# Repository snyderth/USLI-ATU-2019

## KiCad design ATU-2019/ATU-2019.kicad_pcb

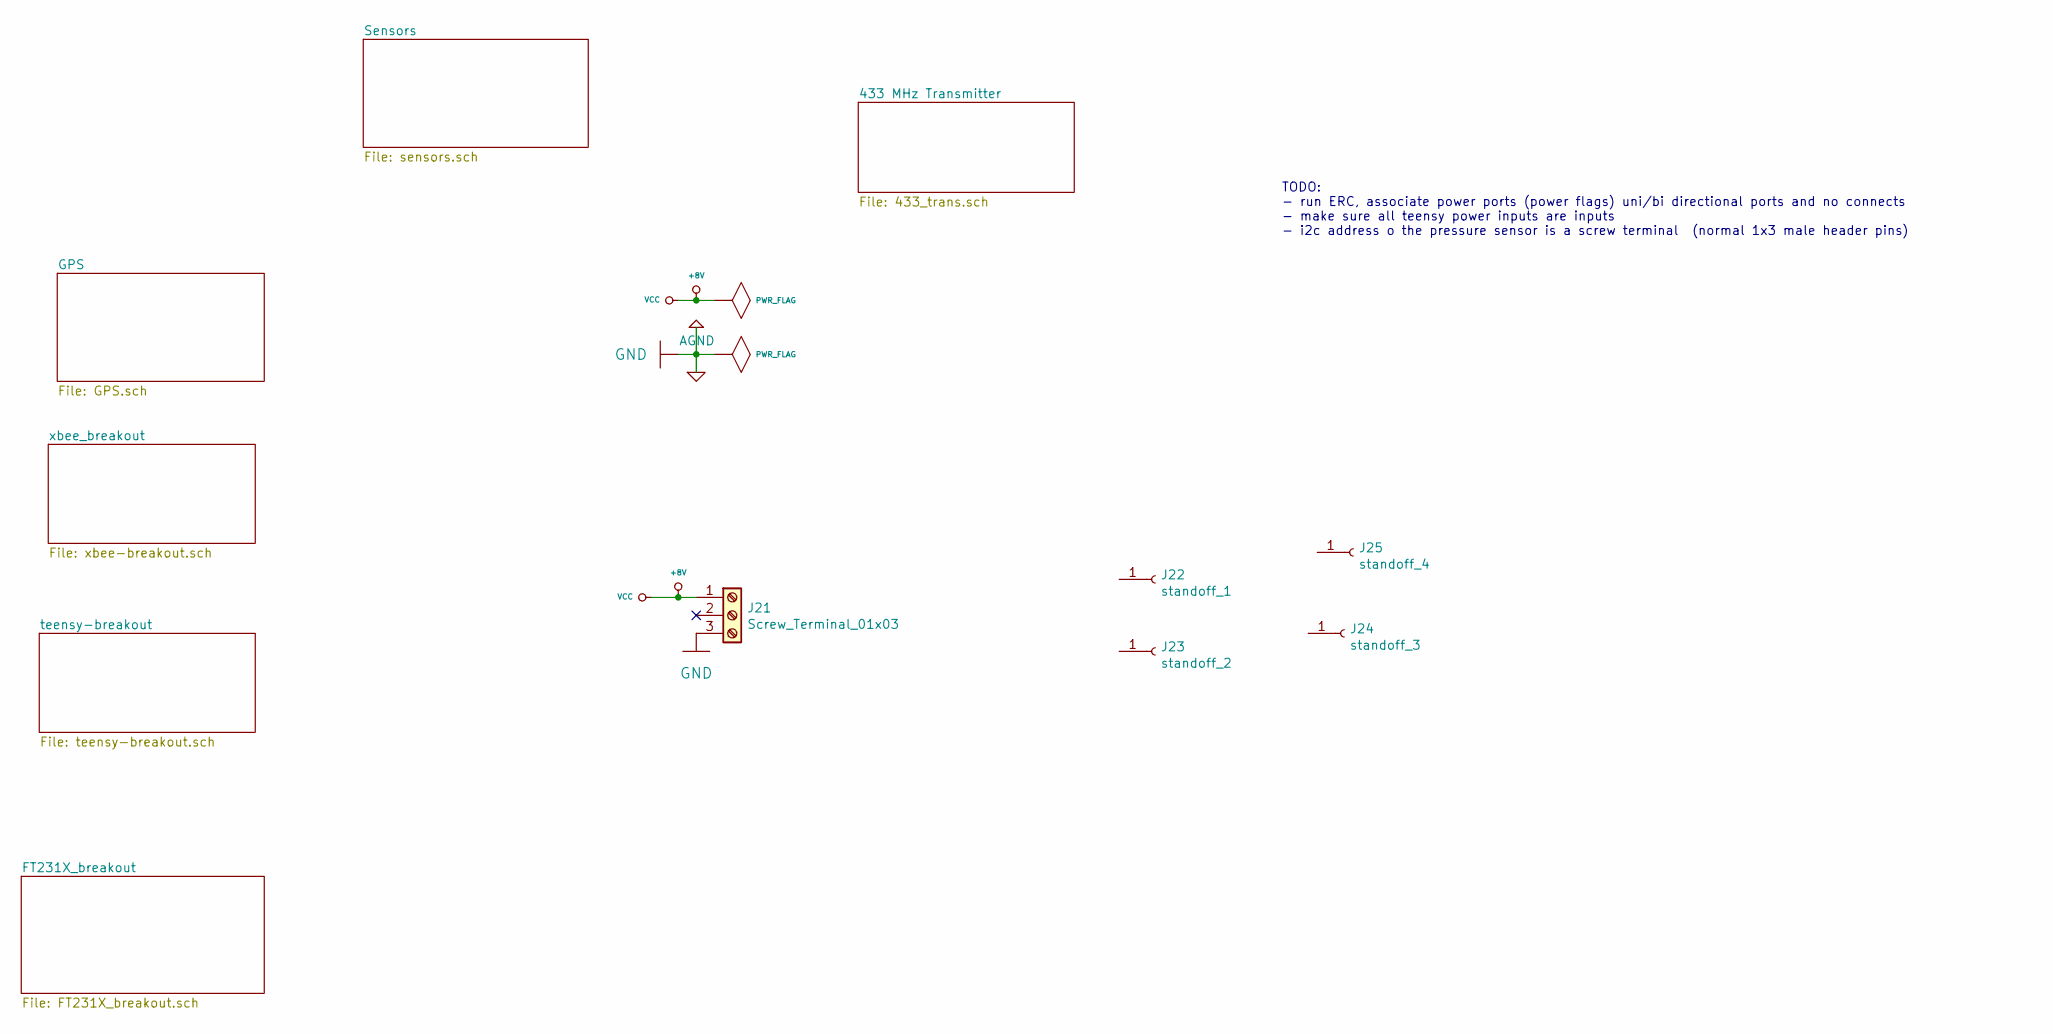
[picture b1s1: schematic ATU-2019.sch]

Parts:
J21: Screw_Terminal_01x03; TerminalBlock_4Ucon_1x03_P3.50mm_Vertical
J22: standoff_1; MountingHole_4.3mm_M4_Pad
J23: standoff_2; MountingHole_4.3mm_M4_Pad
J24: standoff_3; MountingHole_4.3mm_M4_Pad
J25: standoff_4; MountingHole_4.3mm_M4_Pad

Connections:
+8V: J21.1; also elsewhere on the board
AGND: J21.3; also elsewhere on the board

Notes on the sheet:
TODO: - run ERC, associate power ports (power flags) uni/bi directional ports and no connects - make sure all teensy power inputs are inputs - i2c address o the pressure sensor is a screw terminal (normal 1x3 male header pins)

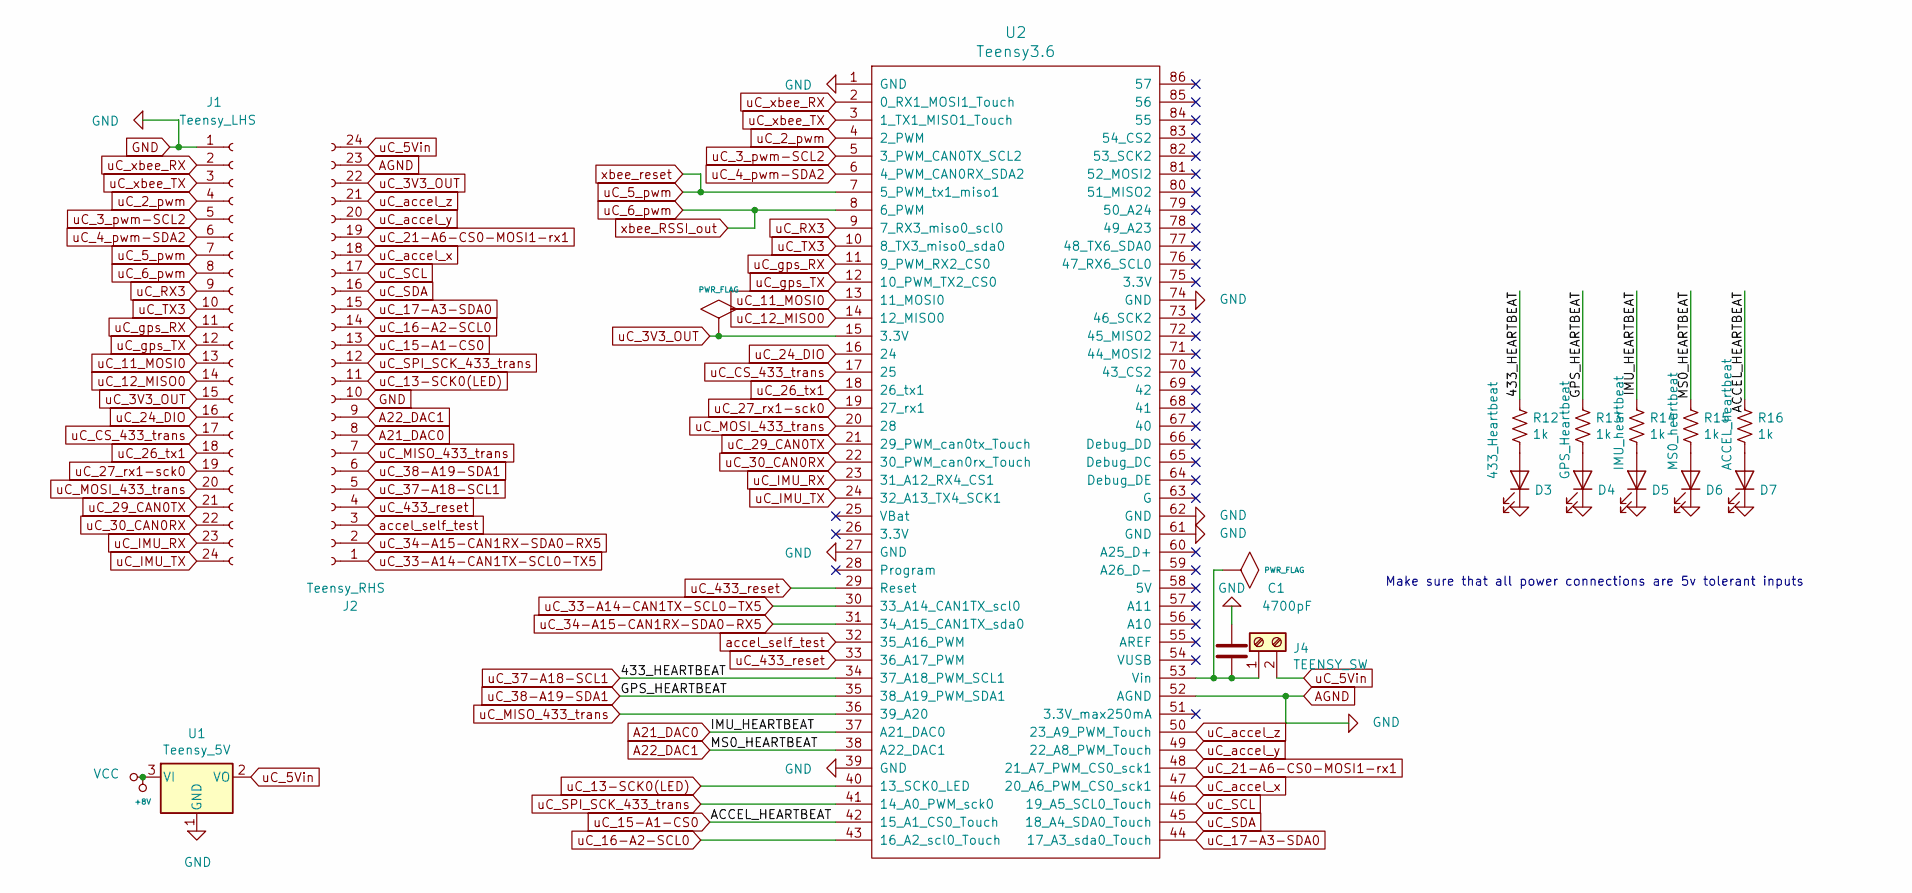
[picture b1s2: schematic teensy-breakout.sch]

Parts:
C1: 4700pF; C_0805_2012Metric_Pad1.15x1.40mm_HandSolder
D3: 433_Heartbeat; LED_0805_2012Metric_Pad1.15x1.40mm_HandSolder
D4: GPS_Heartbeat; LED_0805_2012Metric_Pad1.15x1.40mm_HandSolder
D5: IMU_heartbeat; LED_0805_2012Metric_Pad1.15x1.40mm_HandSolder
D6: MS0_heartbeat; LED_0805_2012Metric_Pad1.15x1.40mm_HandSolder
D7: ACCEL_heartbeat; LED_0805_2012Metric_Pad1.15x1.40mm_HandSolder
J1: Teensy_LHS; PinHeader_1x24_P2.54mm_Vertical
J2: Teensy_RHS; PinHeader_1x24_P2.54mm_Vertical
J4: TEENSY_SW; TerminalBlock_4Ucon_1x02_P3.50mm_Vertical
R12, R13, R14, R15, R16: 1k; R_0805_2012Metric_Pad1.15x1.40mm_HandSolder
U1: Teensy_5V; TO-263-3_TabPin2
U2: Teensy3.6; Teensy35_36

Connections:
+8V: U1.3 (VI); also elsewhere on the board
A21_DAC0: J2.8, R14.1, U2.37 (A21_DAC0)
A22_DAC1: J2.9, R15.1, U2.38 (A22_DAC1)
AGND: C1.2, D3.1 (K), D4.1 (K), D5.1 (K), D6.1 (K), D7.1 (K), J1.1, J2.10, J2.23, U1.1 (GND), U2.1 (GND), U2.27 (GND), U2.39 (GND), U2.52 (AGND), U2.61 (GND), U2.62 (GND), U2.74 (GND); also elsewhere on the board
unnamed: D3.2 (A), R12.2
unnamed: D4.2 (A), R13.2
unnamed: D5.2 (A), R14.2
unnamed: D6.2 (A), R15.2
unnamed: D7.2 (A), R16.2
accel_self_test: J2.3, U2.32 (35_A16_PWM); also elsewhere on the board
uC_2_pwm: J1.4, U2.4 (2_PWM)
uC_3_pwm-SCL2: J1.5, U2.5 (3_PWM_CAN0TX_SCL2)
uC_4_pwm-SDA2: J1.6, U2.6 (4_PWM_CAN0RX_SDA2)
uC_5_pwm: J1.7, U2.7 (5_PWM_tx1_miso1); also elsewhere on the board
uC_6_pwm: J1.8, U2.8 (6_PWM); also elsewhere on the board
uC_11_MOSI0: J1.13, U2.13 (11_MOSI0)
uC_12_MISO0: J1.14, U2.14 (12_MISO0)
uC_13-SCK0(LED): J2.11, U2.40 (13_SCK0_LED)
uC_15-A1-CS0: J2.13, R16.1, U2.42 (15_A1_CS0_Touch)
uC_16-A2-SCL0: J2.14, U2.43 (16_A2_scl0_Touch)
uC_17-A3-SDA0: J2.15, U2.44 (17_A3_sda0_Touch)
uC_21-A6-CS0-MOSI1-rx1: J2.19, U2.48 (21_A7_PWM_CS0_sck1)
uC_24_DIO: J1.16, U2.16 (24)
uC_26_tx1: J1.18, U2.18 (26_tx1)
uC_27_rx1-sck0: J1.19, U2.19 (27_rx1)
uC_29_CAN0TX: J1.21, U2.21 (29_PWM_can0tx_Touch)
uC_30_CAN0RX: J1.22, U2.22 (30_PWM_can0rx_Touch)
uC_33-A14-CAN1TX-SCL0-TX5: J2.1, U2.30 (33_A14_CAN1TX_scl0)
uC_34-A15-CAN1RX-SDA0-RX5: J2.2, U2.31 (34_A15_CAN1TX_sda0)
uC_37-A18-SCL1: J2.5, R12.1, U2.34 (37_A18_PWM_SCL1)
uC_38-A19-SDA1: J2.6, R13.1, U2.35 (38_A19_PWM_SDA1)
uC_CS_433_trans: J1.17, U2.17 (25); also elsewhere on the board
uC_IMU_RX: J1.23, U2.23 (31_A12_RX4_CS1)
uC_IMU_TX: J1.24, U2.24 (32_A13_TX4_SCK1)
uC_MISO_433_trans: J2.7, U2.36 (39_A20); also elsewhere on the board
uC_MOSI_433_trans: J1.20, U2.20 (28); also elsewhere on the board
uC_RX3: J1.9, U2.9 (7_RX3_miso0_scl0)
uC_SCL: J2.17, U2.46 (19_A5_SCL0_Touch); also elsewhere on the board
uC_SDA: J2.16, U2.45 (18_A4_SDA0_Touch); also elsewhere on the board
uC_SPI_SCK_433_trans: J2.12, U2.41 (14_A0_PWM_sck0); also elsewhere on the board
uC_TX3: J1.10, U2.10 (8_TX3_miso0_sda0)
uC_accel_x: J2.18, U2.47 (20_A6_PWM_CS0_sck1); also elsewhere on the board
uC_accel_y: J2.20, U2.49 (22_A8_PWM_Touch); also elsewhere on the board
uC_accel_z: J2.21, U2.50 (23_A9_PWM_Touch); also elsewhere on the board
uC_gps_RX: J1.11, U2.11 (9_PWM_RX2_CS0); also elsewhere on the board
uC_gps_TX: J1.12, U2.12 (10_PWM_TX2_CS0); also elsewhere on the board
uC_xbee_RX: J1.2, U2.2 (0_RX1_MOSI1_Touch); also elsewhere on the board
uC_xbee_TX: J1.3, U2.3 (1_TX1_MISO1_Touch); also elsewhere on the board

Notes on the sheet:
Make sure that all power connections are 5v tolerant inputs

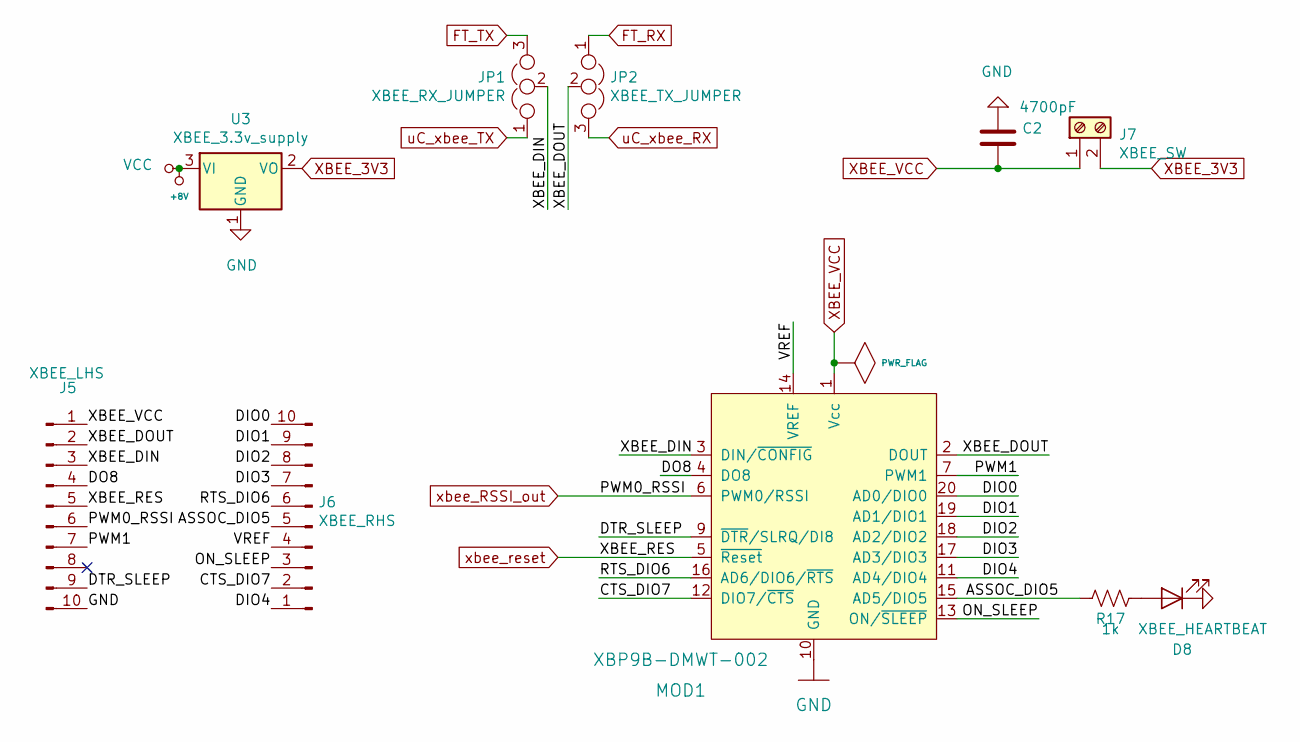
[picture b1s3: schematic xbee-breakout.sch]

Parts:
C2: 4700pF; C_0805_2012Metric_Pad1.15x1.40mm_HandSolder
D8: XBEE_HEARTBEAT; LED_0805_2012Metric_Pad1.15x1.40mm_HandSolder
J5: XBEE_LHS; PinHeader_1x10_P2.54mm_Vertical
J6: XBEE_RHS; PinHeader_1x10_P2.54mm_Vertical
J7: XBEE_SW; TerminalBlock_4Ucon_1x02_P3.50mm_Vertical
JP1: XBEE_RX_JUMPER; TerminalBlock_4Ucon_1x03_P3.50mm_Vertical
JP2: XBEE_TX_JUMPER; TerminalBlock_4Ucon_1x03_P3.50mm_Vertical
MOD1: XBP9B-DMWT-002; XBEE_PRO-20_THT; MPN XBP9B-DMWT-002; Digi-Key_PN 602-1301-ND
R17: 1k; R_0805_2012Metric_Pad1.15x1.40mm_HandSolder
U3: XBEE_3.3v_supply; TO-263-3_TabPin2

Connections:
+8V: U3.3 (VI); also elsewhere on the board
/xbee_breakout/ASSOC_DIO5: J6.5, MOD1.15 (AD5/DIO5), R17.2
/xbee_breakout/CTS_DIO7: J6.2, MOD1.12 (DIO7/~CTS)
/xbee_breakout/DIO0: J6.10, MOD1.20 (AD0/DIO0)
/xbee_breakout/DIO1: J6.9, MOD1.19 (AD1/DIO1)
/xbee_breakout/DIO2: J6.8, MOD1.18 (AD2/DIO2)
/xbee_breakout/DIO3: J6.7, MOD1.17 (AD3/DIO3)
/xbee_breakout/DIO4: J6.1, MOD1.11 (AD4/DIO4)
/xbee_breakout/DO8: J5.4, MOD1.4 (DO8)
/xbee_breakout/DTR_SLEEP: J5.9, MOD1.9 (~DTR~/SLRQ/DI8)
/xbee_breakout/ON_SLEEP: J6.3, MOD1.13 (ON/~SLEEP)
/xbee_breakout/PWM1: J5.7, MOD1.7 (PWM1)
/xbee_breakout/RTS_DIO6: J6.6, MOD1.16 (AD6/DIO6/~RTS)
/xbee_breakout/VREF: J6.4, MOD1.14 (VREF)
/xbee_breakout/XBEE_DIN: J5.3, JP1.2, MOD1.3 (DIN/~CONFIG)
/xbee_breakout/XBEE_DOUT: J5.2, JP2.2, MOD1.2 (DOUT)
AGND: C2.1, D8.1 (K), J5.10, MOD1.10 (GND), U3.1 (GND); also elsewhere on the board
FT_RX: JP2.1; also elsewhere on the board
FT_TX: JP1.3; also elsewhere on the board
unnamed: D8.2 (A), R17.1
XBEE_3V3: J7.2, U3.2 (VO)
XBEE_VCC: C2.2, J5.1, J7.1, MOD1.1 (Vcc)
uC_5_pwm: J5.5, MOD1.5 (~Reset); also elsewhere on the board
uC_6_pwm: J5.6, MOD1.6 (PWM0/RSSI); also elsewhere on the board
uC_xbee_RX: JP2.3; also elsewhere on the board
uC_xbee_TX: JP1.1; also elsewhere on the board

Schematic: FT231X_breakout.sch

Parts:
C3: 0.1uF; C_0805_2012Metric_Pad1.15x1.40mm_HandSolder
C4, C5: 47pF; C_0805_2012Metric_Pad1.15x1.40mm_HandSolder
C40: 4700pF; C_0805_2012Metric_Pad1.15x1.40mm_HandSolder
D1: Yellow; LED_0805_2012Metric_Pad1.15x1.40mm_HandSolder
D2: Red; LED_0805_2012Metric_Pad1.15x1.40mm_HandSolder
J3: FT231X_USB; USB_Micro-B_Wuerth_629105150521_CircularHoles
J8: FT231_SW; TerminalBlock_4Ucon_1x02_P3.50mm_Horizontal
R1, R2: 27; R_0805_2012Metric_Pad1.15x1.40mm_HandSolder
R3, R4: 1k; R_0805_2012Metric_Pad1.15x1.40mm_HandSolder
U5: FT231XS; SSOP-20_3.9x8.7mm_P0.635mm

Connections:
AGND: C3.2, C4.2, C5.2, C40.1, J3.5 (GND), J3.6 (Shield), U5.6 (GND), U5.16 (GND); also elsewhere on the board
FT231X_VBUS: J3.1 (VBUS), J8.2
FT231X_VCC: C40.2, J8.1, U5.15 (VCC)
FT231_3V3OUT: C3.1, D1.2 (A), D2.2 (A), U5.3 (VCCIO), U5.13 (3V3OUT), U5.14 (~RESET)
FT231_D+: R1.1, U5.11 (USBDP)
FT231_D-: R2.2, U5.12 (USBDM)
FT_RX: U5.4 (RXD); also elsewhere on the board
FT_TX: U5.20 (TXD); also elsewhere on the board
unnamed: C4.1, J3.3 (D+), R1.2
unnamed: C5.1, J3.2 (D-), R2.1
unnamed: D1.1 (K), R4.1
unnamed: D2.1 (K), R3.1
unnamed: R3.2, U5.17 (CBUS1)
unnamed: R4.2, U5.10 (CBUS2)

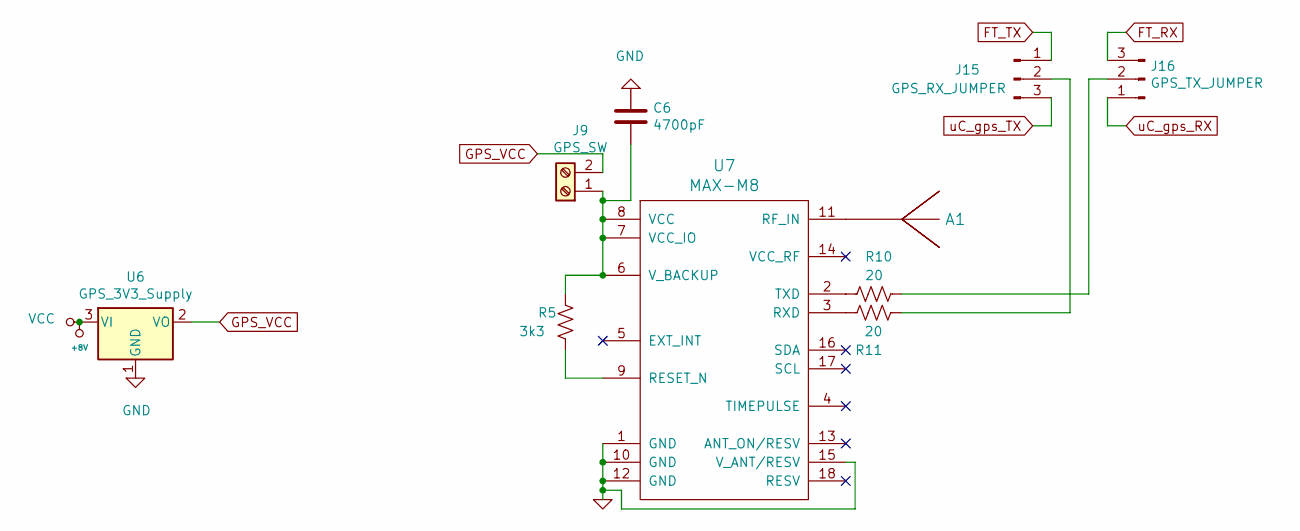
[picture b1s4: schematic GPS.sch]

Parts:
A1: ANTENNA; Patch_Antenna_18mmx18mm
C6: 4700pF; C_0805_2012Metric_Pad1.15x1.40mm_HandSolder
J9: GPS_SW; TerminalBlock_4Ucon_1x02_P3.50mm_Vertical
J15: GPS_RX_JUMPER; TerminalBlock_4Ucon_1x03_P3.50mm_Horizontal
J16: GPS_TX_JUMPER; TerminalBlock_4Ucon_1x03_P3.50mm_Horizontal
R5: 3k3; R_0805_2012Metric_Pad1.15x1.40mm_HandSolder
R10, R11: 20; R_0805_2012Metric_Pad1.15x1.40mm_HandSolder
U6: GPS_3V3_Supply; TO-263-3_TabPin2
U7: MAX-M8

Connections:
+8V: U6.3 (VI); also elsewhere on the board
AGND: C6.1, U6.1 (GND), U7.1 (GND), U7.10 (GND), U7.12 (GND), U7.15 (V_ANT/RESV); also elsewhere on the board
FT_RX: J16.3; also elsewhere on the board
FT_TX: J15.1; also elsewhere on the board
GPS_VCC: J9.2, U6.2 (VO)
unnamed: A1.1, U7.11 (RF_IN)
unnamed: C6.2, J9.1, R5.1, U7.6 (V_BACKUP), U7.7 (VCC_IO), U7.8 (VCC)
unnamed: J15.2, R11.2
unnamed: J16.2, R10.1
unnamed: R5.2, U7.9 (RESET_N)
unnamed: R10.2, U7.2 (TXD)
unnamed: R11.1, U7.3 (RXD)
uC_gps_RX: J16.1; also elsewhere on the board
uC_gps_TX: J15.3; also elsewhere on the board

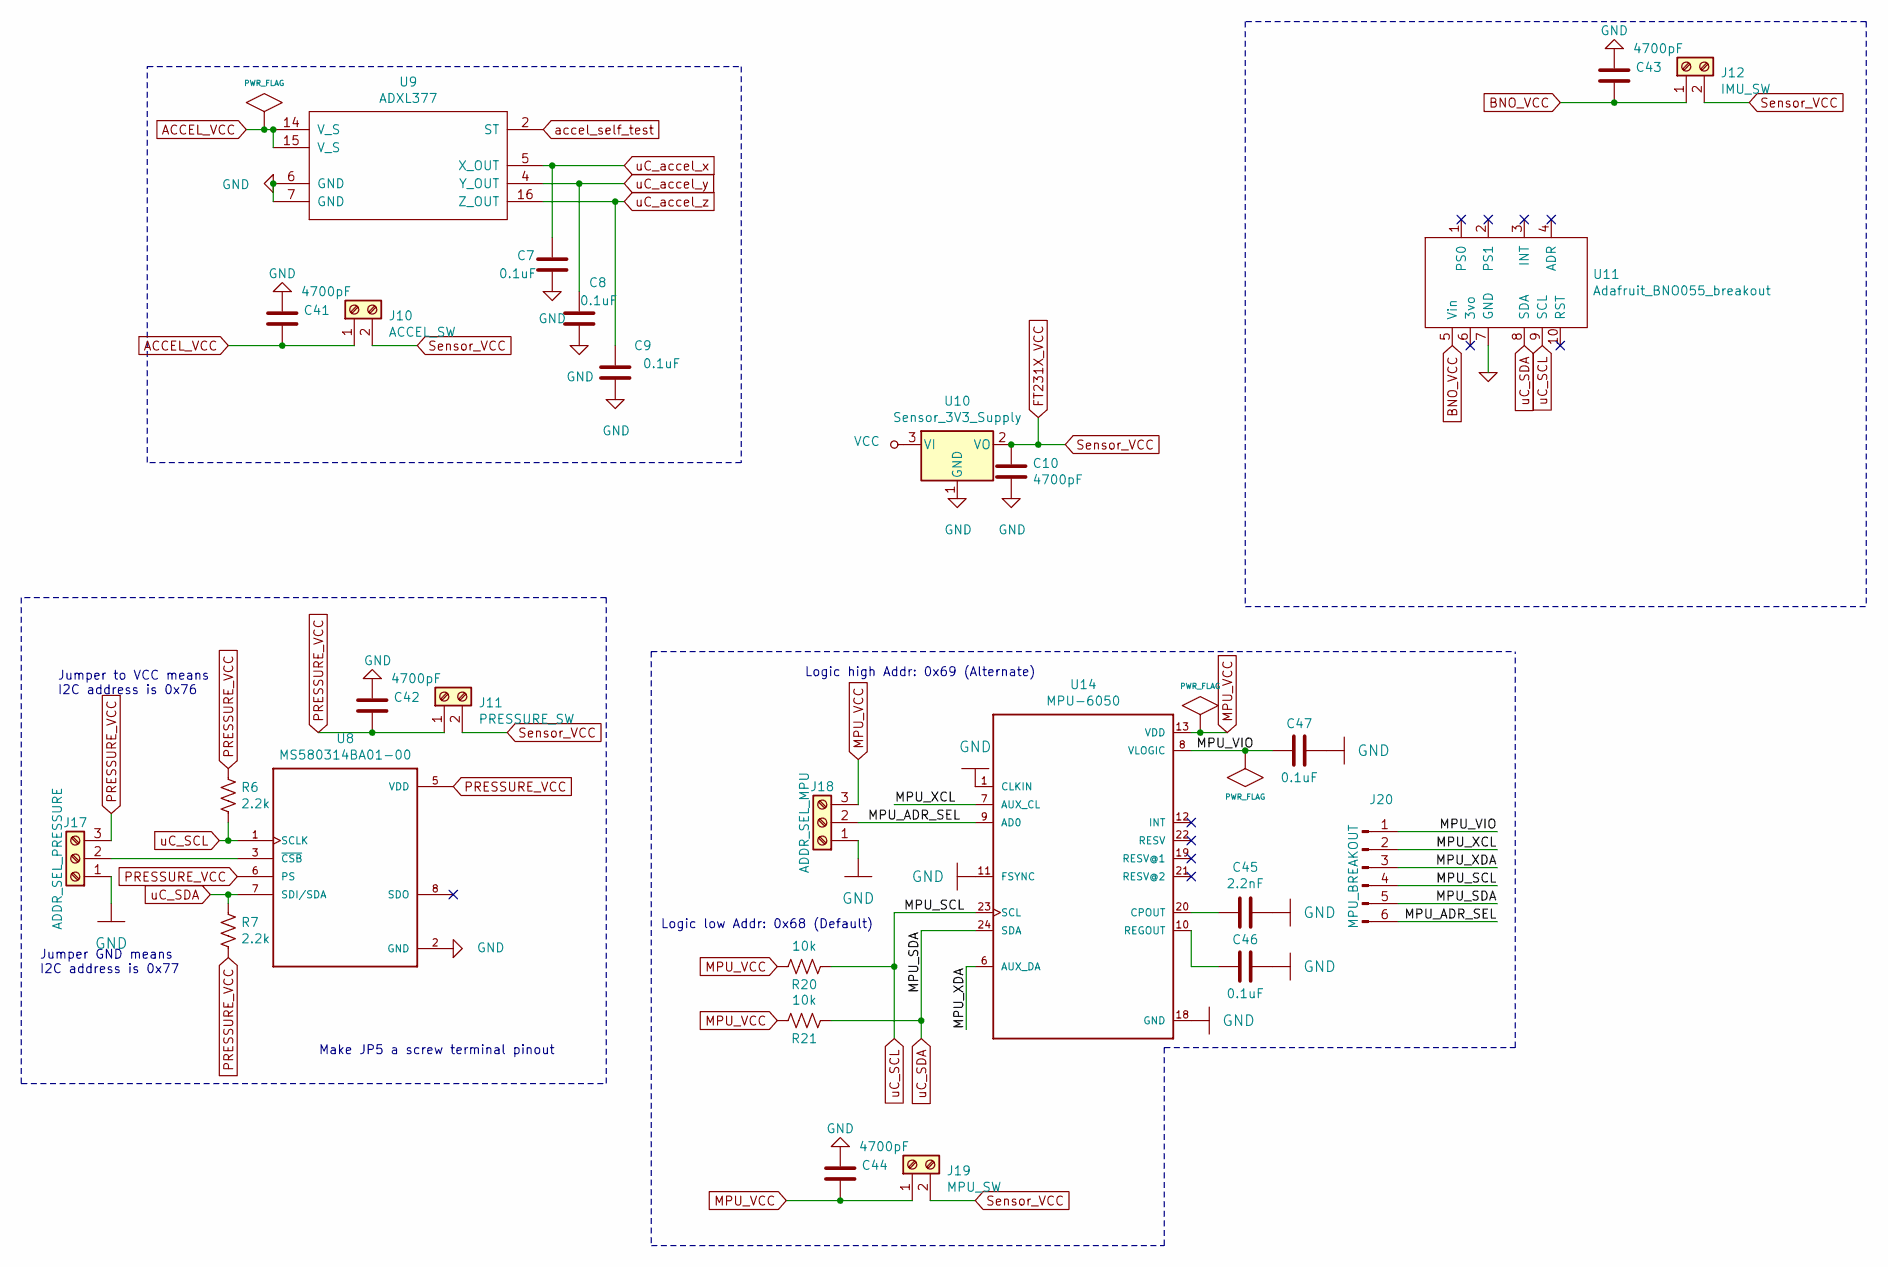
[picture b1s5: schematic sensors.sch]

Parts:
C7, C8, C9, C46, C47: 0.1uF; C_0805_2012Metric_Pad1.15x1.40mm_HandSolder
C10, C41, C42, C43, C44: 4700pF; C_0805_2012Metric_Pad1.15x1.40mm_HandSolder
C45: 2.2nF; C_0805_2012Metric_Pad1.15x1.40mm_HandSolder
J10: ACCEL_SW; TerminalBlock_4Ucon_1x02_P3.50mm_Vertical
J11: PRESSURE_SW; TerminalBlock_4Ucon_1x02_P3.50mm_Vertical
J12: IMU_SW; TerminalBlock_4Ucon_1x02_P3.50mm_Vertical
J17: ADDR_SEL_PRESSURE; TerminalBlock_4Ucon_1x03_P3.50mm_Vertical
J18: ADDR_SEL_MPU; TerminalBlock_4Ucon_1x03_P3.50mm_Vertical
J19: MPU_SW; TerminalBlock_4Ucon_1x02_P3.50mm_Vertical
J20: MPU_BREAKOUT; PinHeader_1x06_P2.54mm_Vertical
R6, R7: 2.2k; R_0805_2012Metric_Pad1.15x1.40mm_HandSolder
R20, R21: 10k; R_0805_2012Metric_Pad1.15x1.40mm_HandSolder
U8: MS580314BA01-00; XDCR_MS580314BA01-00
U9: ADXL377
U10: Sensor_3V3_Supply; TO-263-3_TabPin2
U11: Adafruit_BNO055_breakout
U14: MPU-6050; QFN50P400X400X95-24N

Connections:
+8V: U10.3 (VI); also elsewhere on the board
/Sensors/MPU_ADR_SEL: J18.2, J20.6, U14.9 (AD0)
/Sensors/MPU_VIO: C47.2, J20.1, U14.8 (VLOGIC)
/Sensors/MPU_XCL: J20.2, U14.7 (AUX_CL)
/Sensors/MPU_XDA: J20.3, U14.6 (AUX_DA)
ACCEL_VCC: C41.2, J10.1, U9.14 (V_S), U9.15 (V_S)
AGND: C7.2, C8.2, C9.2, C10.2, C41.1, C42.1, C43.1, C44.1, C45.1, C46.1, C47.1, J17.1, J18.1, U8.2 (GND), U9.6 (GND), U9.7 (GND), U10.1 (GND), U11.7 (GND), U14.1 (CLKIN), U14.11 (FSYNC), U14.18 (GND); also elsewhere on the board
BNO_VCC: C43.2, J12.1, U11.5 (Vin)
MPU_VCC: C44.2, J18.3, J19.1, R20.2, R21.2, U14.13 (VDD)
unnamed: C45.2, U14.20 (CPOUT)
unnamed: C46.2, U14.10 (REGOUT)
unnamed: J17.2, U8.3 (~CSB~)
PRESSURE_VCC: C42.2, J11.1, J17.3, R6.1, R7.2, U8.5 (VDD), U8.6 (PS)
Sensor_VCC: C10.1, J10.2, J11.2, J12.2, J19.2, U10.2 (VO)
accel_self_test: U9.2 (ST); also elsewhere on the board
uC_SCL: J20.4, R6.2, R20.1, U8.1 (SCLK), U11.9 (SCL), U14.23 (SCL); also elsewhere on the board
uC_SDA: J20.5, R7.1, R21.1, U8.7 (SDI/SDA), U11.8 (SDA), U14.24 (SDA); also elsewhere on the board
uC_accel_x: C7.1, U9.5 (X_OUT); also elsewhere on the board
uC_accel_y: C8.1, U9.4 (Y_OUT); also elsewhere on the board
uC_accel_z: C9.1, U9.16 (Z_OUT); also elsewhere on the board

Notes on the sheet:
Jumper GND means I2C address is 0x77
Jumper to VCC means I2C address is 0x76
Make JP5 a screw terminal pinout
Logic low Addr: 0x68 (Default)
Logic high Addr: 0x69 (Alternate)

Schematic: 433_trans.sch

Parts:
C15, C16, C30: 5.1pF; C_0402_1005Metric
C17, C18: 15pF; C_0805_2012Metric_Pad1.15x1.40mm_HandSolder
C19: 1.5nF; C_0805_2012Metric_Pad1.15x1.40mm_HandSolder
C20, C21, C22, C24, C25, C26, C28, C32, C33, C34, C35: 47nF; C_0805_2012Metric_Pad1.15x1.40mm_HandSolder
C23: 39pF; C_0402_1005Metric
C27: 10nF; C_0805_2012Metric_Pad1.15x1.40mm_HandSolder
C29: 2.2pF; C_0402_1005Metric
C31: 220nF; C_0805_2012Metric_Pad1.15x1.40mm_HandSolder
C36: 56pF; C_0402_1005Metric
C37: 6.2pF; C_0402_1005Metric
C38: 10nF; C_0402_1005Metric
C39: 100pF; C_0402_1005Metric
J13: DEBUG_BREAKOUT_433; PinHeader_1x08_P2.54mm_Vertical
J14: CC1200_SW; TerminalBlock_4Ucon_1x02_P3.50mm_Horizontal
L1, L4: 27nH; L_0402_1005Metric
L2, L6: 15nH; L_0402_1005Metric
L3, L5: 56nH; L_0402_1005Metric
L7: 43nH; L_0402_1005Metric
L8: 22nH; L_0402_1005Metric
R8: 56k; R_0805_2012Metric_Pad1.15x1.40mm_HandSolder
R9: 18; R_0402_1005Metric
TP1: TestPoint; test_point_antenna
U12: 433_MHz_3V3; TO-263-3_TabPin2
U13: CC1200RHBT; QFN50P500X500X100-33N
Y2: 40MHz; Crystal_SMD_7050-2Pin_7.0x5.0mm_HandSoldering

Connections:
433_VCC: C20.1, C21.1, C24.1, C26.1, C28.1, C32.1, C33.1, C34.1, C35.1, C36.1, C38.1, C39.1, J14.1, R9.1, U13.1 (VDD_GUARD), U13.5 (DVDD), U13.12 (DVDD), U13.13 (AVDD_IF), U13.15 (AVDD_RF), U13.22 (AVDD_SYNTH1), U13.25 (AVDD_PFD_CHP), U13.27 (AVDD_SYNTH2), U13.28 (AVDD_XOSC)
433_VCC_IN: J14.2, U12.2 (VO)
+8V: U12.3 (VI); also elsewhere on the board
/433 MHz Transmitter/GPIO0: J13.6, U13.10 (GPIO0)
/433 MHz Transmitter/GPIO2: J13.7, U13.4 (GPIO2)
/433 MHz Transmitter/GPIO3: J13.8, U13.3 (GPIO3)
/433 MHz Transmitter/LNA_N: C16.1, L3.2, L4.2, U13.20 (LNA_N)
/433 MHz Transmitter/LNA_P: C15.1, L1.2, L3.1, U13.19 (LNA_P)
/433 MHz Transmitter/TRX_SW: C30.2, L2.1, U13.18 (TRX_SW)
AGND: C16.2, C17.2, C18.2, C20.2, C21.2, C22.2, C24.2, C25.2, C26.2, C27.2, C28.2, C31.2, C32.2, C33.2, C34.2, C35.2, C37.2, C38.2, C39.2, L1.1, R8.2, U12.1 (GND), U13.EXP (GND); also elsewhere on the board
unnamed: C15.2, L2.2, L4.1
unnamed: C17.1, U13.30 (XOSC_Q1), Y2.2
unnamed: C18.1, U13.31 (XOSC_Q2), Y2.1
unnamed: C19.1, U13.23 (LPF0)
unnamed: C19.2, U13.24 (LPF1)
unnamed: C22.1, U13.21 (DCPL_VCO)
unnamed: C23.1, C29.2, L6.1
unnamed: C23.2, L5.1, U13.17 (PA)
unnamed: C25.1, U13.26 (DCPL_PFD_CHP)
unnamed: C27.1, U13.29 (DCPL_XOSC)
unnamed: C29.1, C30.1, L6.2, L7.1
unnamed: C31.1, U13.6 (DCPL)
unnamed: C36.2, L5.2, R9.2
unnamed: C37.1, L7.2, L8.1
unnamed: L8.2, TP1.1
unnamed: R8.1, U13.14 (RBIAS)
uC_CS_433_trans: J13.5, U13.11 (CSN); also elsewhere on the board
uC_MISO_433_trans: J13.4, U13.9 (GPIO1); also elsewhere on the board
uC_MOSI_433_trans: J13.3, U13.7 (SI); also elsewhere on the board
uC_SPI_SCK_433_trans: J13.2, U13.8 (SCLK); also elsewhere on the board

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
